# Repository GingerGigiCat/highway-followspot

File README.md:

# HIGHLIGHT!

## Highlight is my followspot i've designed for hack club's [highway](https://highway.hackclub.com/) hardware event

A **followspot** is a type of spotlight used in theatre which is manually controlled and pointed at an actor. They normally have brightness and zoom controls, which mine has!

It has:

- An over 100W white LED COB chip for over 17000 lumens of light output (Max. 150W, real max depends on how much heat the led dissipates as i'll have to limit it so it can't overheat and die)
- An upcycled camera lens no longer good enough for photography but perfect for a beam of light
- Motorised lens control with manual control if desired and zoom recall
- Digital constant current LED dimming (so no flickering from PWM)
- USB-C for computer control of brightness and zoom
- Fully open source everything
- 3 programmable buttons and a fader
- Automatic brightness reduction if the LED gets too hot
- A light on the control panel to give feedback, like if the main LED is too hot or the lens is being pushed too far

The body is 3D printed in PETG but it could be made out of a better material if you feel like it, and the legs are plywood, and of course the lens is glass.

Here's the onshape link! https://cad.onshape.com/documents/9e98bdcd2562c04de815ecc5/w/89c7868c82d5394c068b4491/e/8808e6d7c01ac629712aeab9?renderMode=0&uiState=6882b91ba27d1511c88b3310

## Why?

I wanted my GCSE Design and Technology project to be a spotlight, but my DT teacher said no and told me to downsize it to a desk lamp. It got me a good grade, but it's not what I wanted to make, so I'm taking the opportunity to make what I want to make, with an LED bright enough to blind my DT teacher! (/j....) I'm going to take inspiration from my project, as I do like the general hexagonal design of it (see below)

I have a passion for the technical parts of theatre, so making this was rather an obvious choice for me

## PCB

## Wiring Diagram

(Made in GIMP :))

## More pictures :)

# Bill of Materials

| Vendor         | Name (link)                          | Description                                                                | Price (Digikey With VAT) | Price (Local)       | Price (LCSC)  | Price(Other)    | Notes                                                                                                         |
| -------------- | ------------------------------------ | -------------------------------------------------------------------------- | ------------------------ | ------------------- | ------------- | --------------- | ------------------------------------------------------------------------------------------------------------- |
| digikey        | [XLG-150-H-AB ](https://www.digikey.co.uk/en/products/detail/mean-well-usa-inc/XLG-150-H-AB/10222586)                        | 150W 27-56V led driver                                                     | £31.04                   |                     | x             |                 |                                                                                                               |
| LCSC           | [IRM-10-5](https://lcsc.com/product-detail/Power-Module-Power-Supply_MW-MEAN-WELL-Enterprises-IRM-10-5_C2857903.html?s_z=n_IRM-10-5)                             | 10W 5V psu                                                                 | x 6.38                   |                     | $4.32         |                 |                                                                                                               |
| digikey        | [SPU03L-12](https://www.digikey.co.uk/en/products/detail/mean-well-usa-inc/SPU03L-12/7707058)                            | 3W 5v to 12v conerter                                                      | £4.51                    |                     |               |                 |                                                                                                               |
| digikey        | [‎CXM-32-50-80-54-AC00-F2-5‎](https://www.digikey.co.uk/en/products/detail/luminus-devices-inc/CXM-32-50-80-54-AC00-F2-5/5811014)                | 50-56V up to 200W LED                                                       | £21.78                   |                     | x             |                 |                                                                                                               |
| digikey        | [K104K15X7RF5TL2](https://www.digikey.co.uk/en/products/detail/vishay-beyschlag-draloric-bc-components/K104K15X7RF5TL2/286538)                      | 0.1uF tht capacitor                                                        | £0.22                    |                     |               |                 |                                                                                                               |
| digikey        | ["885012210006"](https://www.digikey.co.uk/en/products/detail/w%C3%BCrth-elektronik/885012210006/5453247)                       | 10nF smt capacitor                                                         | £0.46                    |                     |               |                 |                                                                                                               |
| digikey        | [PTA6043-2010CIB502](https://www.digikey.co.uk/en/products/detail/bourns-inc/PTA6043-2010CIB502/3781226)                   | 5K slide potentiometer                                                     | £1.70                    |                     | x?            |                 |                                                                                                               |
| LCSC           | [ETA-G-K-24-200cm](https://lcsc.com/product-detail/Electronic-testing-accessories_ETA-ETA-G-K-24-200cm_C5144202.html?s_z=n_ETA-G-K-24)                    | 2m K-type thermocouple bare wires                                          |                          |                     | $4.56         |                 |                                                                                                               |
| LCSC           | [MAX31855KASA+T](https://lcsc.com/product-detail/ADCs-DACs-Special-Purpose_Analog-Devices-Inc-Maxim-Integrated-MAX31855KASA-T_C52028.html)                       | MAX31855 thermocouple amplifier chip                                       | x 8.28                   |                     | $2.33         |                 |                                                                                                               |
| digikey        | [Wuerth elektronik screw pin terminal](https://www.digikey.co.uk/en/products/detail/w%C3%BCrth-elektronik/691137710002/6644051) | Screwy terminal block for 2 pins for thermocouple                          | £0.32                    |                     |               |                 |                                                                                                               |
| digikey        | [xiao rp2040](https://www.digikey.co.uk/en/products/detail/seeed-technology-co-ltd/102010428/14672129)                          | xiao rp2040 microcontroller                                                | £4.15                    |                     | x             |                 |                                                                                                               |
| digikey        | [PC817X2NSZ9F](https://www.digikey.co.uk/en/products/detail/sharp-socle-technology/PC817X2NSZ9F/7942022)                         | pc817 optocoupler/optoisolator                                             | £0.24                    |                     | x $0.38=£0.28 |                 | (LCSC minimum order quantity is 5, for just one it would be $0.07 but alas)                                   |
|                |                                      | 40 ohm resistor for led                                                    | (I have already)         |                     |               | £0.05           | (estimate price)                                                                                              |
|                |                                      | Red led                                                                    | (I have already)         |                     |               | ~5p if you buy? |                                                                                                               |
|                |                                      | 80-100 ohm resistor for optocoupler                                        | (will get locally)       |                     |               | £0.05           | (estimate price)                                                                                              |
|                |                                      | 3x cherry style keyboard switches and keycaps                              | (I have already)         |                     |               | ~5p if you buy? |                                                                                                               |
|                |                                      | 2.5A fuse - possibly 5x20mm                                                | (will get locally)       |                     |               | £0.10           | (estimate price)                                                                                              |
|                |                                      | SG90 servo motor                                                           | (I have already)         |                     |               |                 |                                                                                                               |
| LCSC           | [Legion RT-C14B-H1+SS11-1BB](https://lcsc.com/product-detail/AC-Power-Connectors_Legion-RT-C14B-H1-SS11-1BB_C22379821.html?s_z=n_c14%2520input)           | iec panel mount input with fuse and switch integrated                                 | x 1.45                   |                     | $1.46         |                 | LCSC one has a switch too!                                                                                    |
| digikey        | [xiao pin headers](https://www.digikey.co.uk/en/products/detail/seeed-technology-co-ltd/102010490/19176770)                     | 7 pin headers for xiao rp2040, as well as for the servo                    | £0.22                    | (might get locally) |               |                 |                                                                                                               |
| digikey        | [molex 47053-1000](https://www.digikey.co.uk/en/products/detail/molex/0470531000/2421261?s=N4IgTCBcDaICwHYAMBWAzAWgIxNyAugDQgpSgAOUWx5lkOSAvo0A)                     | 4 pin fan header                                                           | £0.43                    |                     | x             |                 |                                                                                                               |
| digikey        | [ATS-HP-F9L200S70W-014](https://www.digikey.co.uk/en/products/detail/advanced-thermal-solutions-inc/ATS-HP-F9L200S70W-014/5049697?s=N4IgjCBcoOw1oDGUBmBDANgZwKYBoQB7KAbRACYYwA2SkAXQIAcAXKEAZRYCcBLAOwDmIAL4EwATgDMCEMkjps%2BIqQrkALBOoNmbSJx4DhIk0A)                | 200mm long 10.5mm wide ~60W heat pipe - 3 OF THEM                          | £12.90                   |                     |               |                 |                                                                                                               |
| amazon         | [1kg sunlu black petg filament](https://www.amazon.co.uk/SUNLU-Filament-Tangle-Free-Dimensional-Accuracy/dp/B0D1KC72YP)        | 1kg black PETG sunlu filament, for more heat resistance                    |                          |                     |               | £8.75           | (i'm splitting the cost with a friend so i only get 1kg and pay £8.75 for it, normally it would be about £12) |
| vinted         | [Cooler master hyper 212 evo](https://www.vinted.co.uk/items/6787848360-coolmasters-hyper-212-fan)          | heatsink with fan                                                          |                          |                     |               | £9.71          |(previously fb marketplace but the one i was going to get sold)                                                       |
| amazon         | [10g Silicone EC360 Thermal Glue](https://www.amazon.co.uk/EC360%C2%AE-Glue-Thermal-Adhesive-Liquid/dp/B00XQ9AZ8Y)      | Thermally conductive adhesive for attaching heat pipes                     |                          |                     |               | £5.99           |                                                                                                               |
|                |                                      | 50x85mm 3mm mdf                                                            |                          |                     |               | free            |                                                                                                               |
|                |                                      | about 40 m4 bolts and nuts (12mm long mostly but some might be longer)     |                          |                     |               | £6              | (estimate price)                                                                                              |
|                |                                      | 2 m10 bolts and nuts                                                       |                          |                     |               | £6.00           |                                                                                                               |
|                |                                      | about 400x200mm of thick plywood                                           |                          |                     |               | free            |                                                                                                               |
| JLCPCB         |                                      | The pcb!!!                                                                 |                          |                     |               | £12.00          |                                                                                                               |
|                |                                      |                                                                            |                          |                     |               |                 |                                                                                                               |
|                |                                      |                                                                            |                          |                     |               |                 |                                                                                                               |
|                |                                      |                                                                            |                          |                     | $12.45        |                 | Just parts cost                                                                                               |
| shipping stuff |                                      |                                                                            |                          |                     | $10.40        |                 | Shipping cost                                                                                                 |
| Total          |                                      |                                                                            | £78.18                   |                     | $22.85=£16.73 | £48.94          | £144.25                                                                                                       |
|                |                                      |                                                                            |                          |                     | cheaper!      |                 |                                                                                                               |
| Total total    | (manual value input)                 |                                                                            |                          |                     |               |                 | $195.39                                                                                                       |

(I am willing to cover the amount i've gone over budget if i have to)

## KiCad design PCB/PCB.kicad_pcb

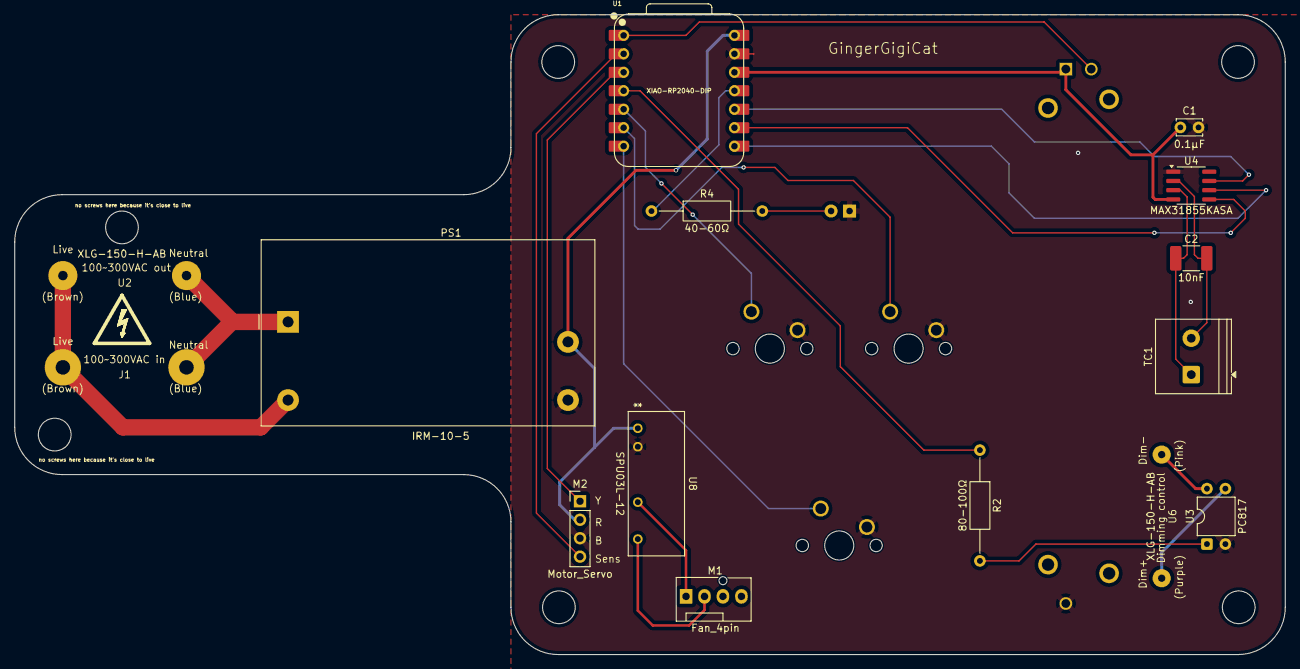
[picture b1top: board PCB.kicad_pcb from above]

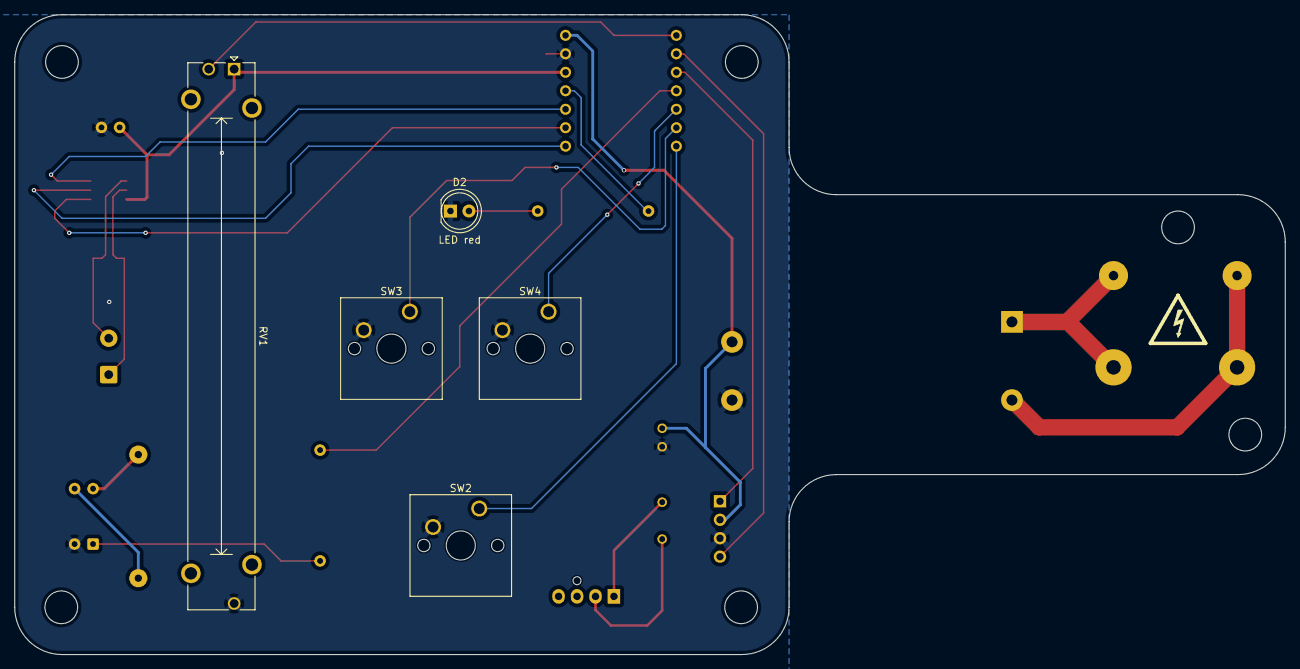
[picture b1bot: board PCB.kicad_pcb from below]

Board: 2 copper layers, 174.8 x 88.0 mm, 20 parts (5 on the bottom side), 24 nets.

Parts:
C1: 0.1µF; C_Disc_D3.4mm_W2.1mm_P2.50mm
C2: 10nF; C_1812_4532Metric_Pad1.57x3.40mm_HandSolder
D2: LED red; LED_D5.0mm
J1: IEC_C14_Receptacle; C14 Power input
M1: Fan_4pin; FanPinHeader_1x04_P2.54mm_Vertical
M2: Motor_Servo; PinHeader_1x04_P2.54mm_Vertical
PS1: IRM-10-5; Converter_ACDC_MeanWell_IRM-10-xx_THT
R2: 80-100Ω; R_Axial_DIN0207_L6.3mm_D2.5mm_P15.24mm_Horizontal
R4: 40-60Ω; R_Axial_DIN0207_L6.3mm_D2.5mm_P15.24mm_Horizontal
RV1: Pot; Potentiometer_Bourns_PTA6043_Single_Slide
SW2: SW_Push SET; SW_Cherry_MX_1.00u_PCB
SW3: SW_Push Pos1; SW_Cherry_MX_1.00u_PCB
SW4: SW_Push Pos2; SW_Cherry_MX_1.00u_PCB
TC1: Thermocouple_Block; TerminalBlock_Philmore_TB132_1x02_P5.00mm_Horizontal
U1: XIAO-RP2040-DIP
U2: XLG-150-H-AB; Meanwell ELG-150-54B AC side
U3: PC817; DIP-4_W7.62mm
U4: MAX31855KASA; SOIC-8_3.9x4.9mm_P1.27mm
U6: Meanwell ELG-150-54B dim pins; Meanwell ELG-150-54B Other Side
U8: SPU03L-12; SPU03L-12_MWU

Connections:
+3V3: C1.1, RV1.1, U1.12 (3V3), U4.4 (V_{CC})
+5V: M2.2 (+), PS1.4 (+Vo), U1.14 (VBUS), U8.1 (VIN+)
GND: C1.2, D2.1 (K), M2.3 (-), PS1.3 (-Vo), RV1.3, SW2.2, SW3.2, SW4.2, U1.13 (GND), U3.2, U4.1 (GND), U8.2 (VIN-)
unnamed: D2.2 (A), R4.2
unnamed: J1.1 (L), PS1.2 (AC/L), U2.1 (L_in)
unnamed: J1.2 (N), PS1.1 (AC/N), U2.2 (N_in)
unnamed: M1.2 (+), U8.7 (VOUT+)
unnamed: M1.1 (-), U8.5 (VOUT-)
unnamed: M2.1 (PWM), U1.3 (GPIO28/ADC2/A2)
unnamed: M2.4 (Sense), U1.2 (GPIO27/ADC1/A1)
unnamed: R2.2, U3.1
unnamed: C2.1, TC1.1 (+), U4.3 (T+)
unnamed: C2.2, TC1.2 (-), U4.2 (T-)
unnamed: SW2.1, U1.7 (GPIO0/TX)
unnamed: U1.8 (GPIO1/RX), U4.6 (~CS)
unnamed: U1.9 (GPIO2/SCK), U4.5 (SCK)
unnamed: R4.1, U1.11 (GPIO3/MOSI)
unnamed: U1.10 (GPIO4/MISO), U4.7 (SO)
unnamed: SW4.1, U1.5 (GPIO6/SDA)
unnamed: SW3.1, U1.6 (GPIO7/SCL)
unnamed: RV1.2, U1.1 (GPIO26/ADC0/A0)
unnamed: R2.1, U1.4 (GPIO29/ADC3/A3)
unnamed: U3.3, U6.1 (Dim+)
unnamed: U3.4, U6.2 (Dim-)

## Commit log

2025-05-17 Create journal.md and first entry
2025-05-17 forgot to finish a sentence :pf:
2025-05-19 Log day 2
2025-05-19 Rename journal.md to JOURNAL.md
2025-05-19 Day 2.5
2025-05-20 added pcb files
2025-05-20 Day uhhh idk the number is it 3?
2025-05-20 numbers
2025-05-20 new meanwell 5v psu instead of mystery box
2025-05-21 fix link
2025-05-21 made pcb better or something, oh yeah and i added the meanwell led driver as a schematic symbol
2025-05-22 day uhhhh
2025-05-22 hoiurs
2025-05-24 from yesterday but i forgot to commit changes
2025-05-24 yippee done the lens holder!!!!
2025-05-26 led platform
2025-05-28 yay yummy servo code, it currently calibrates itself and then deactivates the servo to let you move it manually, and giving serial output of the rotation based on the resistance of the potentiometer 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
2025-05-28 made the code have rotation limiting
2025-05-28 it's a little wonky but it kind of stores positions? it likes to get stuck on the moving the motor and keeps thinking the pin is pressed even though it's not
2025-05-28 MORE
2025-05-28 hhhh
2025-05-29 attempted to fix some of the weirdness with rotation limiting - it no longer randomly decides to jump up, and there's a little less bouncing at the lower limit
2025-05-30 PCB resistor
2025-05-30 apparently the file was changed so i'm pushing it
2025-05-30 pcbing!
2025-06-04 fix typo
2025-06-04 did stuff
2025-06-08 add libraries that i had but didn't add to git
2025-06-20 old changes added
2025-06-20 add all the changes i've made, sorry for not gitting it bit by bit
2025-06-23 fix malformed pcb file
2025-06-29 uhh did stuff by the looks of it
2025-07-04 oops didn't change time logged
2025-07-15 add slight pcb changes
2025-07-21 TIME
2025-07-24 add changed files
2025-07-24 add wiring diagram
2025-07-24 make readme better!!
2025-07-25 add description of what a followspot is because i forgot most people have no idea what that means
2025-07-25 add BoM
2025-07-25 add links to BoM because ag why didn't it just have that in the converter
2025-07-25 add bunch of files and did some code
2025-07-25 timmeeeeee
2025-07-29 code!!!
2025-07-29 bom with links because excel silly
2025-07-30 called it highlight!
2025-08-14 updated readme bom to reflect the cheaper led i actually bought
2025-08-14 Update BoM.csv to reflect the cheaper led i actually bought
2025-08-14 oops forgot to update totals
2025-08-14 Updated to reflect excel spreadsheet and show the vinted cpu cooler
2025-08-15 Update main image
2025-10-19 Add a real picture to readme
